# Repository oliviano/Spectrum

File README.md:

# SPECTRUM

## Arduino Pro Mini LED PWM Controller:

Basic Function:

 * Reads a potentiometre ( aka cheap rotary encoder )
 * Map potentiometre reading to a Hue
 * Signal filtering & Logic
 * Converts Hue, Sat, Brightness to RGB
 * Make Beautiful & playfull light for Sydney VIVId 2016

Pre Requisites:
  * Library Average [link](https://github.com/MajenkoLibraries/Average)

Deployed for Sydney Vivid 2016 artwork "Spectrum"

To Do:
 * Add Average library file or link

 * IP67/68 Connectors -> alibaba led 4pin connectors
 * Calibration TrimPot on board + code + new board
 * Smaller Gauge Cable !!!!!!!
 * Beautify Hue Variation
 * WS281'ing the setup
 * Install a webcam so I can see it from afar.
 * Idle Mode ?

And here's some code!

```CPP
$(function(){
  $('div').html('I am a div.');
});
```

Check the work out  [on Vivid Website](http://www.vividsydney.com/event/light/spectrum) it's the render view, hopefully Vivid changes it sometime.

Shot to all the ressources online, great mind sharing amazing code.

### Stuff used to make this:

 * [markdown editor](https://jbt.github.io/markdown-editor/) for Markdown parsing
 * [hallertau Statesman] (http://www.hallertau.co.nz/craft-beer/#number-2) for making a fine beverage

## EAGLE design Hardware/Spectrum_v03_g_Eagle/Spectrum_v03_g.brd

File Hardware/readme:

- Board layout created with eagle 6.9.74 for OSx 
- Part Library from Sparkfun & Adafruits

- BOM -
Potentiometres - 10K Linear
N-Channel Mosfet - Low Gate Voltage ( micro controller friendly ) 10A - 60V Rated
10K PullDown Resistor for Gate of Mosfet
--
Connectors
Box
12V Power supplier
Cables

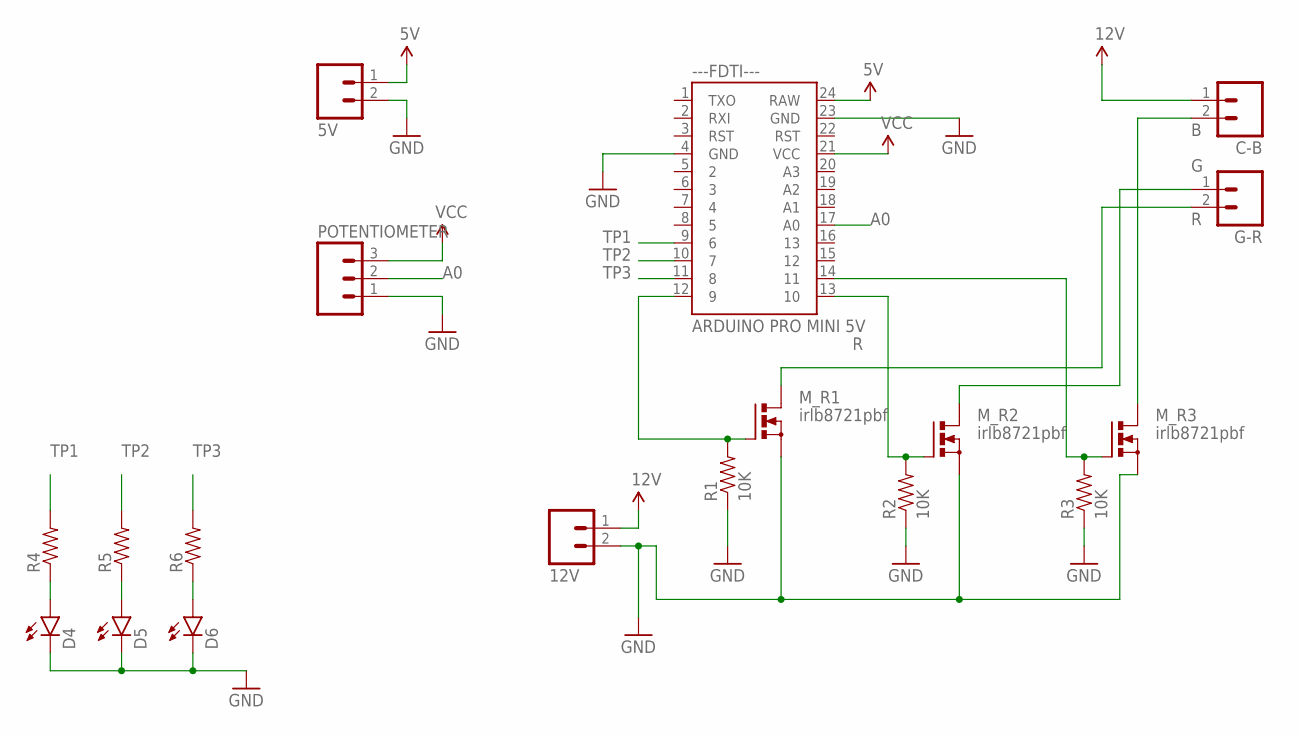
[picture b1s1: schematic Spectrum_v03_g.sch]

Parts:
5V, 12V: M025MM; SCREWTERMINAL-5MM-2
---FDTI---: ARDUINO PRO MINI 5V; ARDUINO_MINI
C-B: M025MM; SCREWTERMINAL-5MM-2
D4, D5, D6: LED3MM
G-R: M025MM; SCREWTERMINAL-5MM-2
M_R1, M_R2, M_R3: irlb8721pbf; TO220BV
POTENTIOMETER: M03-SCREW-5MM; SCREWTERMINAL-5MM-3
R1, R2, R3: 10K; AXIAL-0.4
R4, R5, R6: RESISTOREZ; AXIAL-0.3EZ

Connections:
5V: 5V.1, ---FDTI---.24 (RAW)
12V: 12V.1, C-B.1
A0: ---FDTI---.17 (A0), POTENTIOMETER.2
B: C-B.2, M_R3.D
G: G-R.1, M_R2.D
GND: 5V.2, 12V.2, ---FDTI---.4 (GND), ---FDTI---.23 (GND), D4.K (C), D5.K (C), D6.K (C), M_R1.S, M_R2.S, M_R3.S, POTENTIOMETER.1, R1.P$1 (1), R2.P$1 (1), R3.P$1 (1)
unnamed: ---FDTI---.12 (9), M_R1.G, R1.P$2 (2)
unnamed: ---FDTI---.13 (10), M_R2.G, R2.P$2 (2)
unnamed: ---FDTI---.14 (11), M_R3.G, R3.P$2 (2)
unnamed: D4.A, R4.P$1 (1)
unnamed: D5.A, R5.P$1 (1)
unnamed: D6.A, R6.P$1 (1)
R: G-R.2, M_R1.D
TP1: ---FDTI---.9 (6), R4.P$2 (2)
TP2: ---FDTI---.10 (7), R5.P$2 (2)
TP3: ---FDTI---.11 (8), R6.P$2 (2)
VCC: ---FDTI---.21 (VCC), POTENTIOMETER.3

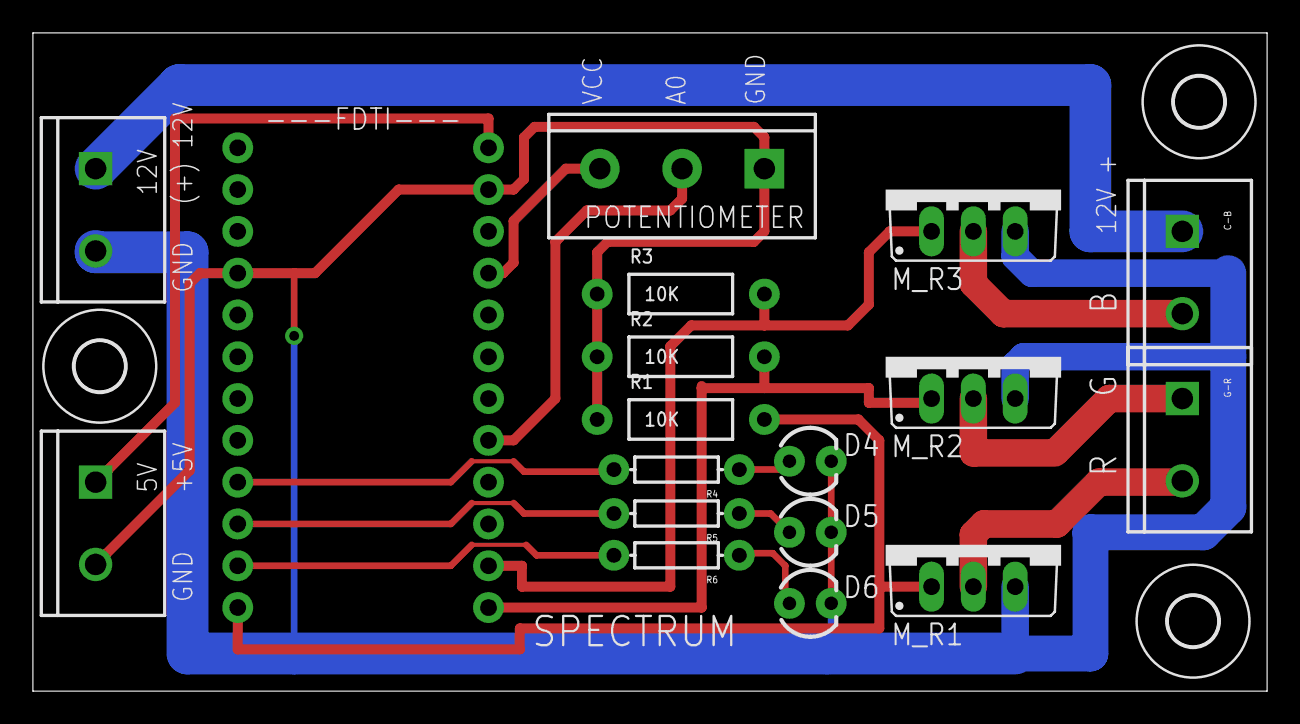
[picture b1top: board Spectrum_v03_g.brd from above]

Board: 2 copper layers, 75.0 x 40.0 mm, 21 parts (0 on the bottom side), 17 nets.

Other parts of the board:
U$2, U$3, U$4: 3,0

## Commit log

2016-06-03 Create readme_arduino
2016-06-03 Initial commit - Arduino Code
2016-06-03 Initial Commit - Eagle Files
2016-06-03 Update Readme
    Added BOM
2017-12-12 README.md
    Added Link to the average library

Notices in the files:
parts and their libraries:
SparkFun-Boards: Licensing: Creative Commons ShareAlike 4.0 International - https://creativecommons.org/licenses/by-sa/4.0
